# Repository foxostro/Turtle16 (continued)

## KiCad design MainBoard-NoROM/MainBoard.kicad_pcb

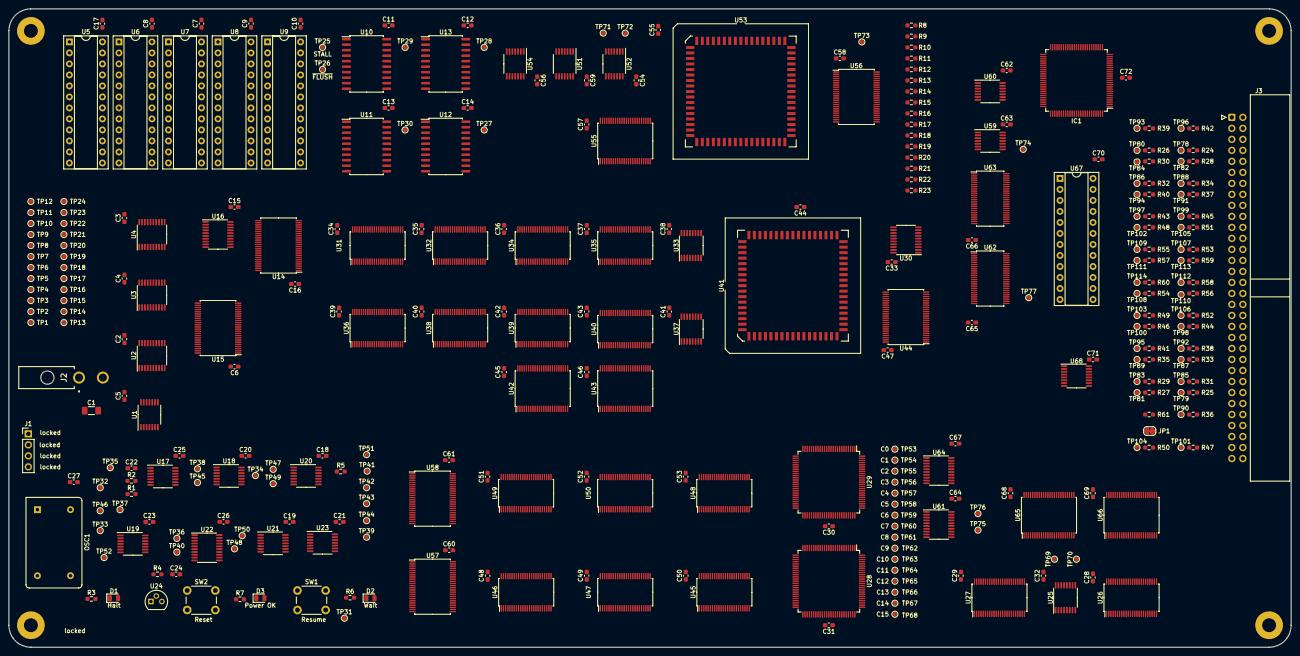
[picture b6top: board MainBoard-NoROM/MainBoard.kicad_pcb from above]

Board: 4 copper layers, 295.9 x 147.3 mm, 330 parts (0 on the bottom side), 505 nets, no tracks yet.

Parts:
C1: 100µF; C_1206_3216Metric_Pad1.33x1.80mm_HandSolder
C2, C3, C4, C5, C6, C7, C8, C9, C10, C11, C12, C13, C14, C15, C16, C17, C18, C19, C20, C21, C23, C24, C25, C26, C27, C28, C29, C30, C31, C32, C33, C34, C35, C36, C37, C38, C39, C40, C41, C42, C43, C44, C45, C46, C47, C48, C49, C50, C51, C52, C53, C54, C55, C56, C57, C58, C59, C60, C61, C62, C63, C64, C65, C66, C67, C68, C69, C70, C71, C72: 100nF; C_0603_1608Metric_Pad1.08x0.95mm_HandSolder
C22: 1uF; C_0603_1608Metric_Pad1.08x0.95mm_HandSolder
D1: Halt; LED_0805_2012Metric
D2: Wait; LED_0805_2012Metric
D3: Power OK; LED_0805_2012Metric
H1, H2, H3, H4: MountingHole_Pad; MountingHole_3.2mm_M3_Pad
IC1: 7028L20PFGI; TQFP-100_14x14mm_P0.5mm
J1: Ext Clock; PinHeader_1x04_P2.54mm_Vertical
J2: Power; 172448-0002
J3: 71922-164LF; IDC-Header_2x32_P2.54mm_Horizontal
JP1: SolderJumper_2_Bridged; SolderJumper-2_P1.3mm_Bridged_RoundedPad1.0x1.5mm
OSC1: 12MHz; Oscillator_DIP-14
R1, R5, R8, R9, R10, R11, R12, R13, R14, R15, R16, R17, R18, R19, R20, R21, R22, R23, R24, R25, R26, R27, R28, R29, R30, R31, R32, R33, R34, R35, R36, R37, R38, R39, R40, R41, R42, R43, R44, R45, R46, R47, R48, R49, R50, R51, R52, R53, R54, R55, R56, R57, R58, R59, R60, R61: 10K; R_0603_1608Metric_Pad0.98x0.95mm_HandSolder
R2, R4: 1K; R_0603_1608Metric_Pad0.98x0.95mm_HandSolder
R3, R6, R7: 270R; R_0603_1608Metric_Pad0.98x0.95mm_HandSolder
SW1: Resume; SW_PUSH_6mm_H5mm
SW2: Reset; SW_PUSH_6mm_H5mm
TP1: Ctl_Mid0; TestPoint_Pad_D1.0mm
TP2: Ctl_Mid1; TestPoint_Pad_D1.0mm
TP3: Ctl_Mid2; TestPoint_Pad_D1.0mm
TP4: Ctl_Mid3; TestPoint_Pad_D1.0mm
TP5: Ctl_Mid4; TestPoint_Pad_D1.0mm
TP6: Ctl_Mid5; TestPoint_Pad_D1.0mm
TP7: Ctl_Mid6; TestPoint_Pad_D1.0mm
TP8: Ctl_Mid7; TestPoint_Pad_D1.0mm
TP9: Ctl_Mid8; TestPoint_Pad_D1.0mm
TP10: Ctl_Mid9; TestPoint_Pad_D1.0mm
TP11: Ctl_Mid10; TestPoint_Pad_D1.0mm
TP12: Ctl_Mid11; TestPoint_Pad_D1.0mm
TP13: Ctl_Mid12; TestPoint_Pad_D1.0mm
TP14: Ctl_Mid13; TestPoint_Pad_D1.0mm
TP15: Ctl_Mid14; TestPoint_Pad_D1.0mm
TP16: Ctl_Mid15; TestPoint_Pad_D1.0mm
TP17: Ctl_Mid16; TestPoint_Pad_D1.0mm
TP18: Ctl_Mid17; TestPoint_Pad_D1.0mm
TP19: Ctl_Mid18; TestPoint_Pad_D1.0mm
TP20: Ctl_Mid19; TestPoint_Pad_D1.0mm
TP21: Ctl_Mid20; TestPoint_Pad_D1.0mm
TP22: Ctl_Mid21; TestPoint_Pad_D1.0mm
TP23: Ctl_Mid22; TestPoint_Pad_D1.0mm
TP24: Ctl_Mid23; TestPoint_Pad_D1.0mm
TP25: STALL; TestPoint_Pad_D1.0mm
TP26: ~{FLUSH}; TestPoint_Pad_D1.0mm
TP27: SEL_B_MATCHES_SEL_C_MEM; TestPoint_Pad_D1.0mm
TP28: SEL_A_MATCHES_SEL_C_MEM; TestPoint_Pad_D1.0mm
TP29: SEL_A_MATCHES_SEL_C_EX; TestPoint_Pad_D1.0mm
TP30: SEL_B_MATCHES_SEL_C_EX; TestPoint_Pad_D1.0mm
TP31: Resume; TestPoint_Pad_D1.0mm
TP32: RawClock; TestPoint_Pad_D1.0mm
TP33: ~{HLT}; TestPoint_Pad_D1.0mm
TP34, TP38: HLT; TestPoint_Pad_D1.0mm
TP35, TP40, TP41, TP47, TP49, TP50, TP69, TP70, TP71: TP; TestPoint_Pad_D1.0mm
TP36: Phi1_0; TestPoint_Pad_D1.0mm
TP37: Debounced; TestPoint_Pad_D1.0mm
TP39: Button1; TestPoint_Pad_D1.0mm
TP42: Phi1a; TestPoint_Pad_D1.0mm
TP43: Phi1b; TestPoint_Pad_D1.0mm
TP44: Phi1c; TestPoint_Pad_D1.0mm
TP45: Phi1d; TestPoint_Pad_D1.0mm
TP46: Phi2; TestPoint_Pad_D1.0mm
TP48: ~{RST_sync}; TestPoint_Pad_D1.0mm
TP51: RDY; TestPoint_Pad_D1.0mm
TP52: ~{RST_async}; TestPoint_Pad_D1.0mm
TP53: C0; TestPoint_Pad_D1.0mm
TP54: C1; TestPoint_Pad_D1.0mm
TP55: C2; TestPoint_Pad_D1.0mm
TP56: C3; TestPoint_Pad_D1.0mm
TP57: C4; TestPoint_Pad_D1.0mm
TP58: C5; TestPoint_Pad_D1.0mm
TP59: C6; TestPoint_Pad_D1.0mm
TP60: C7; TestPoint_Pad_D1.0mm
TP61: C8; TestPoint_Pad_D1.0mm
TP62: C9; TestPoint_Pad_D1.0mm
TP63: C10; TestPoint_Pad_D1.0mm
TP64: C11; TestPoint_Pad_D1.0mm
TP65: C12; TestPoint_Pad_D1.0mm
TP66: C13; TestPoint_Pad_D1.0mm
TP67: C14; TestPoint_Pad_D1.0mm
TP68: C15; TestPoint_Pad_D1.0mm
TP72: RS1; TestPoint_Pad_D1.0mm
TP73: CLK; TestPoint_Pad_D1.0mm
TP74: ~{RDY}; TestPoint_Pad_D1.0mm
TP75: ~{MemStoreIn}; TestPoint_Pad_D1.0mm
TP76: ~{MemLoadIn}; TestPoint_Pad_D1.0mm
TP77: ~{Assert}; TestPoint_Pad_D1.0mm
TP78: Addr0; TestPoint_Pad_D1.0mm
TP79: IO0; TestPoint_Pad_D1.0mm
TP80: Addr1; TestPoint_Pad_D1.0mm
TP81: IO1; TestPoint_Pad_D1.0mm
TP82: Addr2; TestPoint_Pad_D1.0mm
TP83: IO2; TestPoint_Pad_D1.0mm
TP84: Addr3; TestPoint_Pad_D1.0mm
TP85: IO3; TestPoint_Pad_D1.0mm
TP86: Addr4; TestPoint_Pad_D1.0mm
TP87: IO4; TestPoint_Pad_D1.0mm
TP88: Addr5; TestPoint_Pad_D1.0mm
TP89: IO5; TestPoint_Pad_D1.0mm
TP90: Bank0; TestPoint_Pad_D1.0mm
TP91: Addr6; TestPoint_Pad_D1.0mm
TP92: IO6; TestPoint_Pad_D1.0mm
TP93: Bank1; TestPoint_Pad_D1.0mm
TP94: Addr7; TestPoint_Pad_D1.0mm
TP95: IO7; TestPoint_Pad_D1.0mm
TP96: Bank2; TestPoint_Pad_D1.0mm
TP97: Addr8; TestPoint_Pad_D1.0mm
TP98: IO8; TestPoint_Pad_D1.0mm
TP99: Addr9; TestPoint_Pad_D1.0mm
TP100: IO9; TestPoint_Pad_D1.0mm
TP101: ~{MemStore}; TestPoint_Pad_D1.0mm
TP102: Addr10; TestPoint_Pad_D1.0mm
TP103: IO10; TestPoint_Pad_D1.0mm
TP104: ~{MemLoad}; TestPoint_Pad_D1.0mm
TP105: Addr11; TestPoint_Pad_D1.0mm
TP106: IO11; TestPoint_Pad_D1.0mm
TP107: Addr12; TestPoint_Pad_D1.0mm
TP108: IO12; TestPoint_Pad_D1.0mm
TP109: Addr13; TestPoint_Pad_D1.0mm
TP110: IO13; TestPoint_Pad_D1.0mm
TP111: Addr14; TestPoint_Pad_D1.0mm
TP112: IO14; TestPoint_Pad_D1.0mm
TP113: Addr15; TestPoint_Pad_D1.0mm
TP114: IO15; TestPoint_Pad_D1.0mm
U1, U19, U21, U52, U60: 74AHCT04; TSSOP-14_4.4x5mm_P0.65mm
U2, U3, U4, U22: 74AHCT273; TSSOP-20_4.4x6.5mm_P0.65mm
U5, U6, U7, U8, U9: ATF22V10C-7PX; DIP-24_W7.62mm_Socket
U10, U11, U12, U13: 74F521; SOIC-20W_7.5x12.8mm_P1.27mm
U14, U15, U42, U43, U44, U55, U56, U57, U58, U65, U66: 74ABT16374; TSSOP-48_8x12.5mm_P0.5mm
U16: 74AHCT574; TSSOP-20_4.4x6.5mm_P0.65mm
U17: 74HC14; TSSOP-14_4.4x5mm_P0.65mm
U18, U23: 74AHCT08; TSSOP-14_4.4x5mm_P0.65mm
U20: 74AHCT05; TSSOP-14_4.4x5mm_P0.65mm
U24: MCP100-450D; TO-92
U25, U33, U37: 74AHCT138; TSSOP-16_4.4x5mm_P0.65mm
U26, U27: 74ABT16245; TSSOP-48_6.1x12.5mm_P0.5mm
U28, U29: IDT7024L15PFG; TQFP-100_14x14mm_P0.5mm
U30: 74ABT377; TSSOP-20_4.4x6.5mm_P0.65mm
U31, U32, U34, U35, U36, U38, U39, U40, U45, U46, U47, U48, U49, U50, U62, U63: 74AHCT16245; TSSOP-48_6.1x12.5mm_P0.5mm
U41, U53: IDT7381; PLCC-68_SMD-Socket
U51, U54, U59: 74ABT32; TSSOP-14_4.4x5mm_P0.65mm
U61: 74AHCT245; TSSOP-20_4.4x6.5mm_P0.65mm
U64: 74ABT574; TSSOP-20_4.4x6.5mm_P0.65mm
U67: ATF22V10C; DIP-24_W7.62mm_Socket
U68: CD74HC173PWR; TSSOP-16_4.4x5mm_P0.65mm

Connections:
/Clock/Button1: TP39.1, U18.9, U22.2 (Q0), U22.4 (D1)
/Clock/Phi1_0: TP36.1, U17.4, U21.1, U22.11 (Cp)
/Clock/RawClock: J1.2, OSC1.8 (OUT), TP32.1, U17.3
/Clock/~RST_async: TP52.1, U19.13, U22.1 (~Mr), U22.18 (D7), U24.1 (~RST)
/Clock/~SINGLE: J1.4, U18.12
/EX/A0: U41.1 (A0), U57.2 (1Q1)
/EX/A1: U41.2 (A1), U57.3 (1Q2)
/EX/A2: U41.3 (A2), U57.5 (1Q3)
/EX/A3: U41.4 (A3), U57.6 (1Q4)
/EX/A4: U41.5 (A4), U57.8 (1Q5)
/EX/A5: U41.6 (A5), U57.9 (1Q6)
/EX/A6: U41.7 (A6), U57.11 (1Q7)
/EX/A7: U41.8 (A7), U57.12 (1Q8)
/EX/A8: U41.9 (A8), U57.13 (2Q1)
/EX/A9: U41.10 (A9), U57.14 (2Q2)
/EX/A10: U41.11 (A10), U57.16 (2Q3)
/EX/A11: U41.12 (A11), U57.17 (2Q4)
/EX/A12: U41.13 (A12), U57.19 (2Q5)
/EX/A13: U41.14 (A13), U57.20 (2Q6)
/EX/A14: U41.15 (A14), U57.22 (2Q7)
/EX/A15: U41.16 (A15), U57.23 (2Q8)
/EX/ALU/C16: U30.3 (D0), U41.20 (C16)
/EX/ALU/OVF: U30.7 (D2), U41.24 (OVF)
/EX/ALU/RightOp0: U31.2 (1B1), U32.2 (1B1), U34.2 (1B1), U35.2 (1B1), U41.53 (B0)
/EX/ALU/RightOp1: U31.3 (1B2), U32.3 (1B2), U34.3 (1B2), U35.3 (1B2), U41.54 (B1)
/EX/ALU/RightOp2: U31.5 (1B3), U32.5 (1B3), U34.5 (1B3), U35.5 (1B3), U41.55 (B2)
/EX/ALU/RightOp3: U31.6 (1B4), U32.6 (1B4), U34.6 (1B4), U35.6 (1B4), U41.56 (B3)
/EX/ALU/RightOp4: U31.8 (1B5), U32.8 (1B5), U34.8 (1B5), U35.8 (1B5), U41.57 (B4)
/EX/ALU/RightOp5: U31.9 (1B6), U32.9 (1B6), U34.9 (1B6), U35.9 (1B6), U41.58 (B5)
/EX/ALU/RightOp6: U31.11 (1B7), U32.11 (1B7), U34.11 (1B7), U35.11 (1B7), U41.59 (B6)
/EX/ALU/RightOp7: U31.12 (1B8), U32.12 (1B8), U34.12 (1B8), U35.12 (1B8), U41.60 (B7)
/EX/ALU/RightOp8: U31.13 (2B1), U32.13 (2B1), U34.13 (2B1), U35.13 (2B1), U41.61 (B8)
/EX/ALU/RightOp9: U31.14 (2B2), U32.14 (2B2), U34.14 (2B2), U35.14 (2B2), U41.62 (B9)
/EX/ALU/RightOp10: U31.16 (2B3), U32.16 (2B3), U34.16 (2B3), U35.16 (2B3), U41.63 (B10)
/EX/ALU/RightOp11: U31.17 (2B4), U32.17 (2B4), U34.17 (2B4), U35.17 (2B4), U41.64 (B11)
/EX/ALU/RightOp12: U31.19 (2B5), U32.19 (2B5), U34.19 (2B5), U35.19 (2B5), U41.65 (B12)
/EX/ALU/RightOp13: U31.20 (2B6), U32.20 (2B6), U34.20 (2B6), U35.20 (2B6), U41.66 (B13)
/EX/ALU/RightOp14: U31.22 (2B7), U32.22 (2B7), U34.22 (2B7), U35.22 (2B7), U41.67 (B14)
/EX/ALU/RightOp15: U31.23 (2B8), U32.23 (2B8), U34.23 (2B8), U35.23 (2B8), U41.68 (B15)
/EX/ALU/Z: U30.4 (D1), U41.23 (Z)
/EX/B0: U31.47 (1A1), U36.47 (1A1), U58.2 (1Q1)
/EX/B1: U31.46 (1A2), U36.46 (1A2), U58.3 (1Q2)
/EX/B2: U31.44 (1A3), U36.44 (1A3), U58.5 (1Q3)
/EX/B3: U31.43 (1A4), U36.43 (1A4), U58.6 (1Q4)
/EX/B4: U31.41 (1A5), U36.41 (1A5), U58.8 (1Q5)
/EX/B5: U31.40 (1A6), U36.40 (1A6), U58.9 (1Q6)
/EX/B6: U31.38 (1A7), U36.38 (1A7), U58.11 (1Q7)
/EX/B7: U31.37 (1A8), U36.37 (1A8), U58.12 (1Q8)
/EX/B8: U31.36 (2A1), U36.36 (2A1), U58.13 (2Q1)
/EX/B9: U31.35 (2A2), U36.35 (2A2), U58.14 (2Q2)
/EX/B10: U31.33 (2A3), U36.33 (2A3), U58.16 (2Q3)
/EX/B11: U31.32 (2A4), U36.32 (2A4), U58.17 (2Q4)
/EX/B12: U31.30 (2A5), U36.30 (2A5), U58.19 (2Q5)
/EX/B13: U31.29 (2A6), U36.29 (2A6), U58.20 (2Q6)
/EX/B14: U31.27 (2A7), U36.27 (2A7), U58.22 (2Q7)
/EX/B15: U31.26 (2A8), U36.26 (2A8), U58.23 (2Q8)
/EX/Carry: U5.4 (IN), U6.4 (IN), U7.4 (IN), U30.2 (Q0)
/EX/Ctl_MEM14: TP76.1, U42.2 (1Q1), U61.3 (A1)
/EX/Ctl_MEM15: TP75.1, U42.3 (1Q2), U61.2 (A0)
/EX/Ctl_MEM16: U42.5 (1Q3), U59.5
/EX/Ctl_MEM17: U8.4 (IN), U42.6 (1Q4), U64.9 (D7)
/EX/Ctl_MEM18: U42.8 (1Q5), U64.8 (D6)
/EX/Ctl_MEM19: U42.9 (1Q6), U64.7 (D5)
/EX/Ctl_MEM20: U8.5 (IN), U42.11 (1Q7), U64.6 (D4)
/EX/N: U5.1 (IN/CLK), U6.1 (IN/CLK), U7.1 (IN/CLK), U30.9 (Q3)
/EX/OVF: U5.2 (IN), U6.2 (IN), U7.2 (IN), U30.6 (Q2)
/EX/PC_EX0: U38.47 (1A1), U55.2 (1Q1)
/EX/PC_EX1: U38.46 (1A2), U55.3 (1Q2)
/EX/PC_EX2: U38.44 (1A3), U55.5 (1Q3)
/EX/PC_EX3: U38.43 (1A4), U55.6 (1Q4)
/EX/PC_EX4: U38.41 (1A5), U55.8 (1Q5)
/EX/PC_EX5: U38.40 (1A6), U55.9 (1Q6)
/EX/PC_EX6: U38.38 (1A7), U55.11 (1Q7)
/EX/PC_EX7: U38.37 (1A8), U55.12 (1Q8)
/EX/PC_EX8: U38.36 (2A1), U55.13 (2Q1)
/EX/PC_EX9: U38.35 (2A2), U55.14 (2Q2)
/EX/PC_EX10: U38.33 (2A3), U55.16 (2Q3)
/EX/PC_EX11: U38.32 (2A4), U55.17 (2Q4)
/EX/PC_EX12: U38.30 (2A5), U55.19 (2Q5)
/EX/PC_EX13: U38.29 (2A6), U55.20 (2Q6)
/EX/PC_EX14: U38.27 (2A7), U55.22 (2Q7)
/EX/PC_EX15: U38.26 (2A8), U55.23 (2Q8)
/EX/SelC_MEM0: U12.3 (Q0), U13.3 (Q0), U42.13 (2Q1), U64.5 (D3)
/EX/SelC_MEM1: U12.5 (Q1), U13.5 (Q1), U42.14 (2Q2), U64.4 (D2)
/EX/SelC_MEM2: U12.7 (Q2), U13.7 (Q2), U42.16 (2Q3), U64.3 (D1)
/EX/StoreOp_MEM0: U43.2 (1Q1), U62.23 (2B8)
/EX/StoreOp_MEM1: U43.3 (1Q2), U62.22 (2B7)
/EX/StoreOp_MEM2: U43.5 (1Q3), U62.20 (2B6)
/EX/StoreOp_MEM3: U43.6 (1Q4), U62.19 (2B5)
/EX/StoreOp_MEM4: U43.8 (1Q5), U62.17 (2B4)
/EX/StoreOp_MEM5: U43.9 (1Q6), U62.16 (2B3)
/EX/StoreOp_MEM6: U43.11 (1Q7), U62.14 (2B2)
/EX/StoreOp_MEM7: U43.12 (1Q8), U62.13 (2B1)
/EX/StoreOp_MEM8: U43.13 (2Q1), U62.12 (1B8)
/EX/StoreOp_MEM9: U43.14 (2Q2), U62.11 (1B7)
/EX/StoreOp_MEM10: U43.16 (2Q3), U62.9 (1B6)
/EX/StoreOp_MEM11: U43.17 (2Q4), U62.8 (1B5)
/EX/StoreOp_MEM12: U43.19 (2Q5), U62.6 (1B4)
/EX/StoreOp_MEM13: U43.20 (2Q6), U62.5 (1B3)
/EX/StoreOp_MEM14: U43.22 (2Q7), U62.3 (1B2)
/EX/StoreOp_MEM15: U43.23 (2Q8), U62.2 (1B1)
/EX/Y_EX0: U41.43 (F0), U44.47 (1D1), U46.47 (1A1), U49.47 (1A1), U53.53 (B0)
/EX/Y_EX1: U41.42 (F1), U44.46 (1D2), U46.46 (1A2), U49.46 (1A2), U53.54 (B1)
/EX/Y_EX2: U41.41 (F2), U44.44 (1D3), U46.44 (1A3), U49.44 (1A3), U53.55 (B2)
/EX/Y_EX3: U41.40 (F3), U44.43 (1D4), U46.43 (1A4), U49.43 (1A4), U53.56 (B3)
/EX/Y_EX4: U41.39 (F4), U44.41 (1D5), U46.41 (1A5), U49.41 (1A5), U53.57 (B4)
/EX/Y_EX5: U41.38 (F5), U44.40 (1D6), U46.40 (1A6), U49.40 (1A6), U53.58 (B5)
/EX/Y_EX6: U41.37 (F6), U44.38 (1D7), U46.38 (1A7), U49.38 (1A7), U53.59 (B6)
/EX/Y_EX7: U41.36 (F7), U44.37 (1D8), U46.37 (1A8), U49.37 (1A8), U53.60 (B7)
/EX/Y_EX8: U41.35 (F8), U44.36 (2D1), U46.36 (2A1), U49.36 (2A1), U53.61 (B8)
/EX/Y_EX9: U41.34 (F9), U44.35 (2D2), U46.35 (2A2), U49.35 (2A2), U53.62 (B9)
/EX/Y_EX10: U41.33 (F10), U44.33 (2D3), U46.33 (2A3), U49.33 (2A3), U53.63 (B10)
/EX/Y_EX11: U41.32 (F11), U44.32 (2D4), U46.32 (2A4), U49.32 (2A4), U53.64 (B11)
/EX/Y_EX12: U41.31 (F12), U44.30 (2D5), U46.30 (2A5), U49.30 (2A5), U53.65 (B12)
/EX/Y_EX13: U41.30 (F13), U44.29 (2D6), U46.29 (2A6), U49.29 (2A6), U53.66 (B13)
/EX/Y_EX14: U41.29 (F14), U44.27 (2D7), U46.27 (2A7), U49.27 (2A7), U53.67 (B14)
/EX/Y_EX15: U30.8 (D3), U41.28 (F15), U44.26 (2D8), U46.26 (2A8), U49.26 (2A8), U53.68 (B15)
/EX/Y_MEM0: U44.2 (1Q1), U47.47 (1A1), U50.47 (1A1), U63.2 (1B1), U66.47 (1D1)
/EX/Y_MEM1: U44.3 (1Q2), U47.46 (1A2), U50.46 (1A2), U63.3 (1B2), U66.46 (1D2)
/EX/Y_MEM2: U44.5 (1Q3), U47.44 (1A3), U50.44 (1A3), U63.5 (1B3), U66.44 (1D3)
/EX/Y_MEM3: U44.6 (1Q4), U47.43 (1A4), U50.43 (1A4), U63.6 (1B4), U66.43 (1D4)
/EX/Y_MEM4: U44.8 (1Q5), U47.41 (1A5), U50.41 (1A5), U63.8 (1B5), U66.41 (1D5)
/EX/Y_MEM5: U44.9 (1Q6), U47.40 (1A6), U50.40 (1A6), U63.9 (1B6), U66.40 (1D6)
/EX/Y_MEM6: U44.11 (1Q7), U47.38 (1A7), U50.38 (1A7), U63.11 (1B7), U66.38 (1D7)
/EX/Y_MEM7: U44.12 (1Q8), U47.37 (1A8), U50.37 (1A8), U63.12 (1B8), U66.37 (1D8)
/EX/Y_MEM8: U44.13 (2Q1), U47.36 (2A1), U50.36 (2A1), U63.13 (2B1), U66.36 (2D1)
/EX/Y_MEM9: U44.14 (2Q2), U47.35 (2A2), U50.35 (2A2), U63.14 (2B2), U66.35 (2D2)
/EX/Y_MEM10: U44.16 (2Q3), U47.33 (2A3), U50.33 (2A3), U63.16 (2B3), U66.33 (2D3)
/EX/Y_MEM11: U44.17 (2Q4), U47.32 (2A4), U50.32 (2A4), U63.17 (2B4), U66.32 (2D4)
/EX/Y_MEM12: U44.19 (2Q5), U47.30 (2A5), U50.30 (2A5), U63.19 (2B5), U66.30 (2D5)
/EX/Y_MEM13: U44.20 (2Q6), U47.29 (2A6), U50.29 (2A6), U63.20 (2B6), U66.29 (2D6)
/EX/Y_MEM14: U44.22 (2Q7), U47.27 (2A7), U50.27 (2A7), U63.22 (2B7), U66.27 (2D7)
/EX/Y_MEM15: U44.23 (2Q8), U47.26 (2A8), U50.26 (2A8), U63.23 (2B8), U66.26 (2D8)
/EX/Z: U5.3 (IN), U6.3 (IN), U7.3 (IN), U30.5 (Q1)
/EX/sheet5FD8D6EA/StoreOp_EX0: U36.2 (1B1), U38.2 (1B1), U39.2 (1B1), U40.2 (1B1), U43.47 (1D1)
/EX/sheet5FD8D6EA/StoreOp_EX1: U36.3 (1B2), U38.3 (1B2), U39.3 (1B2), U40.3 (1B2), U43.46 (1D2)
/EX/sheet5FD8D6EA/StoreOp_EX2: U36.5 (1B3), U38.5 (1B3), U39.5 (1B3), U40.5 (1B3), U43.44 (1D3)
/EX/sheet5FD8D6EA/StoreOp_EX3: U36.6 (1B4), U38.6 (1B4), U39.6 (1B4), U40.6 (1B4), U43.43 (1D4)
/EX/sheet5FD8D6EA/StoreOp_EX4: U36.8 (1B5), U38.8 (1B5), U39.8 (1B5), U40.8 (1B5), U43.41 (1D5)
/EX/sheet5FD8D6EA/StoreOp_EX5: U36.9 (1B6), U38.9 (1B6), U39.9 (1B6), U40.9 (1B6), U43.40 (1D6)
/EX/sheet5FD8D6EA/StoreOp_EX6: U36.11 (1B7), U38.11 (1B7), U39.11 (1B7), U40.11 (1B7), U43.38 (1D7)
/EX/sheet5FD8D6EA/StoreOp_EX7: U36.12 (1B8), U38.12 (1B8), U39.12 (1B8), U40.12 (1B8), U43.37 (1D8)
/EX/sheet5FD8D6EA/StoreOp_EX8: U36.13 (2B1), U38.13 (2B1), U39.13 (2B1), U40.13 (2B1), U43.36 (2D1)
/EX/sheet5FD8D6EA/StoreOp_EX9: U36.14 (2B2), U38.14 (2B2), U39.14 (2B2), U40.14 (2B2), U43.35 (2D2)
/EX/sheet5FD8D6EA/StoreOp_EX10: U36.16 (2B3), U38.16 (2B3), U39.16 (2B3), U40.16 (2B3), U43.33 (2D3)
/EX/sheet5FD8D6EA/StoreOp_EX11: U36.17 (2B4), U38.17 (2B4), U39.17 (2B4), U40.17 (2B4), U43.32 (2D4)
/EX/sheet5FD8D6EA/StoreOp_EX12: U36.19 (2B5), U38.19 (2B5), U39.19 (2B5), U40.19 (2B5), U43.30 (2D5)
/EX/sheet5FD8D6EA/StoreOp_EX13: U36.20 (2B6), U38.20 (2B6), U39.20 (2B6), U40.20 (2B6), U43.29 (2D6)
/EX/sheet5FD8D6EA/StoreOp_EX14: U36.22 (2B7), U38.22 (2B7), U39.22 (2B7), U40.22 (2B7), U43.27 (2D7)
/EX/sheet5FD8D6EA/StoreOp_EX15: U36.23 (2B8), U38.23 (2B8), U39.23 (2B8), U40.23 (2B8), U43.26 (2D8)
/ID/Ctl_EX0: TP33.1, U15.2 (1Q1), U18.13, U19.5
/ID/Ctl_EX1: U15.3 (1Q2), U37.1 (A0)
/ID/Ctl_EX2: U15.5 (1Q3), U37.2 (A1)
/ID/Ctl_EX3: U15.6 (1Q4), U33.1 (A0)
/ID/Ctl_EX4: U15.8 (1Q5), U33.2 (A1)
/ID/Ctl_EX5: U15.9 (1Q6), U30.1 (~E)
/ID/Ctl_EX6: U15.11 (1Q7), U41.44 (C0)
/ID/Ctl_EX7: U15.12 (1Q8), U41.45 (I0)
/ID/Ctl_EX8: U15.13 (2Q1), U41.46 (I1)
/ID/Ctl_EX9: U15.14 (2Q2), U41.47 (I2)
/ID/Ctl_EX10: U15.16 (2Q3), U41.48 (RS0)
/ID/Ctl_EX11: U15.17 (2Q4), U41.49 (RS1)
/ID/Ctl_EX12: U15.19 (2Q5), U52.1, U53.44 (C0)
/ID/Ctl_EX13: U15.20 (2Q6), U53.48 (RS0)
/ID/Ctl_EX14: U15.22 (2Q7), U42.47 (1D1)
/ID/Ctl_EX15: U15.23 (2Q8), U42.46 (1D2)
/ID/Ctl_EX16: U16.12 (Q7), U42.44 (1D3)
/ID/Ctl_EX17: U16.13 (Q6), U42.43 (1D4)
/ID/Ctl_EX18: U16.14 (Q5), U42.41 (1D5)
/ID/Ctl_EX19: U16.15 (Q4), U42.40 (1D6)
/ID/Ctl_EX20: U16.16 (Q3), U42.38 (1D7)
/ID/Ctl_Mid0: TP1.1, U2.3 (D0), U5.23 (I/O)
/ID/Ctl_Mid1: TP2.1, U2.4 (D1), U5.22 (I/O)
/ID/Ctl_Mid2: TP3.1, U2.7 (D2), U5.21 (I/O)
/ID/Ctl_Mid3: TP4.1, U2.8 (D3), U5.20 (I/O)
/ID/Ctl_Mid4: TP5.1, U2.13 (D4), U5.19 (I/O)
/ID/Ctl_Mid5: TP6.1, U2.14 (D5), U5.18 (I/O), U9.4 (IN)
/ID/Ctl_Mid6: TP7.1, U2.17 (D6), U5.17 (I/O)
/ID/Ctl_Mid7: TP8.1, U2.18 (D7), U5.14 (I/O)
/ID/Ctl_Mid8: TP9.1, U3.3 (D0), U5.15 (I/O)
/ID/Ctl_Mid9: TP10.1, U3.4 (D1), U5.16 (I/O)
/ID/Ctl_Mid10: TP11.1, U3.7 (D2), U6.21 (I/O)
/ID/Ctl_Mid11: TP12.1, U3.8 (D3), U6.22 (I/O)
/ID/Ctl_Mid12: TP13.1, U3.13 (D4), U6.23 (I/O), U9.5 (IN)
/ID/Ctl_Mid13: TP14.1, U3.14 (D5), U6.20 (I/O)
/ID/Ctl_Mid14: TP15.1, U3.17 (D6), U6.19 (I/O)
/ID/Ctl_Mid15: TP16.1, U3.18 (D7), U6.18 (I/O)
/ID/Ctl_Mid16: TP17.1, U4.3 (D0), U6.17 (I/O)
/ID/Ctl_Mid17: TP18.1, U4.4 (D1), U6.16 (I/O), U8.2 (IN)
/ID/Ctl_Mid18: TP19.1, U4.7 (D2), U6.15 (I/O)
/ID/Ctl_Mid19: TP20.1, U4.8 (D3), U6.14 (I/O)
/ID/Ctl_Mid20: TP21.1, U4.13 (D4), U7.23 (I/O), U8.3 (IN)
/ID/Ctl_Mid21: TP22.1, U4.14 (D5), U7.22 (I/O), U8.10 (IN)
/ID/Ctl_Mid22: TP23.1, U4.17 (D6), U7.21 (I/O), U8.11 (IN)
/ID/Ctl_Mid23: TP24.1, U4.18 (D7), U7.20 (I/O)
/ID/FWD_A: U8.21 (I/O), U45.25 (2~OE), U45.48 (1~OE)
/ID/FWD_B: U8.20 (I/O), U48.25 (2~OE), U48.48 (1~OE)
/ID/FWD_EX_TO_A: U8.22 (I/O), U46.25 (2~OE), U46.48 (1~OE)
/ID/FWD_EX_TO_B: U8.19 (I/O), U49.25 (2~OE), U49.48 (1~OE)
/ID/FWD_MEM_TO_A: U8.23 (I/O), U47.25 (2~OE), U47.48 (1~OE)
/ID/FWD_MEM_TO_B: U8.18 (I/O), U50.25 (2~OE), U50.48 (1~OE)
/ID/Hazard Control/Hazard Control Comparators/SEL_A_MATCHES_SEL_C_EX: TP29.1, U8.6 (IN), U10.19 (~P=Q)
/ID/Hazard Control/Hazard Control Comparators/SEL_A_MATCHES_SEL_C_MEM: TP28.1, U8.8 (IN), U13.19 (~P=Q)
/ID/Hazard Control/Hazard Control Comparators/SEL_B_MATCHES_SEL_C_EX: TP30.1, U8.7 (IN), U11.19 (~P=Q)
/ID/Hazard Control/Hazard Control Comparators/SEL_B_MATCHES_SEL_C_MEM: TP27.1, U8.9 (IN), U12.19 (~P=Q)
/ID/Hazard Control/STALL: TP25.1, U9.23 (I/O), U53.25 (~ENF), U54.2
/ID/Hazard Control/~FLUSH: TP26.1, U2.1 (~Mr), U3.1 (~Mr), U4.1 (~Mr), U9.22 (I/O)
/ID/ID Flush/Ctl_ID0: U2.2 (Q0), U15.47 (1D1)
/ID/ID Flush/Ctl_ID1: U2.5 (Q1), U15.46 (1D2)
/ID/ID Flush/Ctl_ID2: U2.6 (Q2), U15.44 (1D3)
/ID/ID Flush/Ctl_ID3: U2.9 (Q3), U15.43 (1D4)
/ID/ID Flush/Ctl_ID4: U2.12 (Q4), U15.41 (1D5)
/ID/ID Flush/Ctl_ID5: U2.15 (Q5), U15.40 (1D6)
/ID/ID Flush/Ctl_ID6: U2.16 (Q6), U15.38 (1D7)
/ID/ID Flush/Ctl_ID7: U2.19 (Q7), U15.37 (1D8)
/ID/ID Flush/Ctl_ID8: U3.2 (Q0), U15.36 (2D1)
/ID/ID Flush/Ctl_ID9: U3.5 (Q1), U15.35 (2D2)
/ID/ID Flush/Ctl_ID10: U3.6 (Q2), U15.33 (2D3)
/ID/ID Flush/Ctl_ID11: U3.9 (Q3), U15.32 (2D4)
/ID/ID Flush/Ctl_ID12: U3.12 (Q4), U15.30 (2D5)
/ID/ID Flush/Ctl_ID13: U3.15 (Q5), U15.29 (2D6)
/ID/ID Flush/Ctl_ID14: U3.16 (Q6), U15.27 (2D7)
/ID/ID Flush/Ctl_ID15: U3.19 (Q7), U15.26 (2D8)
/ID/ID Flush/Ctl_ID16: U4.2 (Q0), U16.9 (D7)
/ID/ID Flush/Ctl_ID17: U4.5 (Q1), U16.8 (D6)
/ID/ID Flush/Ctl_ID18: U4.6 (Q2), U16.7 (D5)
/ID/ID Flush/Ctl_ID19: U4.9 (Q3), U16.6 (D4)
/ID/ID Flush/Ctl_ID20: U4.12 (Q4), U16.5 (D3)
/ID/ID Flush/Ctl_ID21: U4.15 (Q5), U16.4 (D2)
/ID/ID Flush/Ctl_ID22: U4.16 (Q6), U16.3 (D1)
/ID/ID Flush/Ctl_ID23: U4.19 (Q7), U16.2 (D0)
/ID/Ins_EX0: U14.2 (1Q1), U32.47 (1A1), U34.47 (1A1), U35.47 (1A1), U39.47 (1A1), U40.36 (2A1)
/ID/Ins_EX1: U14.3 (1Q2), U32.46 (1A2), U34.46 (1A2), U35.46 (1A2), U39.46 (1A2), U40.35 (2A2)
/ID/Ins_EX2: U14.5 (1Q3), U32.44 (1A3), U35.44 (1A3), U39.44 (1A3), U40.33 (2A3)
/ID/Ins_EX3: U14.6 (1Q4), U32.43 (1A4), U35.43 (1A4), U39.43 (1A4), U40.32 (2A4)
/ID/Ins_EX4: U14.8 (1Q5), U32.26 (2A8), U32.27 (2A7), U32.29 (2A6), U32.30 (2A5), U32.32 (2A4), U32.33 (2A3), U32.35 (2A2), U32.36 (2A1), U32.37 (1A8), U32.38 (1A7), U32.40 (1A6), U32.41 (1A5), U35.41 (1A5), U39.41 (1A5), U40.30 (2A5)
/ID/Ins_EX5: U14.9 (1Q6), U35.40 (1A6), U39.40 (1A6), U40.29 (2A6)
/ID/Ins_EX6: U14.11 (1Q7), U35.38 (1A7), U39.38 (1A7), U40.27 (2A7)
/ID/Ins_EX7: U14.12 (1Q8), U35.37 (1A8), U39.26 (2A8), U39.27 (2A7), U39.29 (2A6), U39.30 (2A5), U39.32 (2A4), U39.33 (2A3), U39.35 (2A2), U39.36 (2A1), U39.37 (1A8), U40.26 (2A8)
/ID/Ins_EX8: U10.3 (Q0), U11.3 (Q0), U14.13 (2Q1), U34.44 (1A3), U35.36 (2A1), U42.36 (2D1)
/ID/Ins_EX9: U10.5 (Q1), U11.5 (Q1), U14.14 (2Q2), U34.43 (1A4), U35.35 (2A2), U42.35 (2D2)
/ID/Ins_EX10: U10.7 (Q2), U11.7 (Q2), U14.16 (2Q3), U34.26 (2A8), U34.27 (2A7), U34.29 (2A6), U34.30 (2A5), U34.32 (2A4), U34.33 (2A3), U34.35 (2A2), U34.36 (2A1), U34.37 (1A8), U34.38 (1A7), U34.40 (1A6), U34.41 (1A5), U35.26 (2A8), U35.27 (2A7), U35.29 (2A6), U35.30 (2A5), U35.32 (2A4), U35.33 (2A3), U42.33 (2D3)
/ID/Ins_ID0: U14.47 (1D1), U56.2 (1Q1)
/ID/Ins_ID1: U14.46 (1D2), U56.3 (1Q2)
/ID/Ins_ID2: U11.2 (P0), U12.2 (P0), U14.44 (1D3), U29.59 (A0R), U56.5 (1Q3)
/ID/Ins_ID3: U11.4 (P1), U12.4 (P1), U14.43 (1D4), U29.58 (A1R), U56.6 (1Q4)
/ID/Ins_ID4: U11.6 (P2), U12.6 (P2), U14.41 (1D5), U29.57 (A2R), U56.8 (1Q5)
/ID/Ins_ID5: U10.2 (P0), U13.2 (P0), U14.40 (1D6), U28.59 (A0R), U56.9 (1Q6)
/ID/Ins_ID6: U10.4 (P1), U13.4 (P1), U14.38 (1D7), U28.58 (A1R), U56.11 (1Q7)
/ID/Ins_ID7: U10.6 (P2), U13.6 (P2), U14.37 (1D8), U28.57 (A2R), U56.12 (1Q8)
/ID/Ins_ID8: U14.36 (2D1), U56.13 (2Q1)
/ID/Ins_ID9: U14.35 (2D2), U56.14 (2Q2)
/ID/Ins_ID10: U14.33 (2D3), U56.16 (2Q3)
/ID/Ins_ID11: U5.9 (IN), U6.9 (IN), U7.9 (IN), U56.17 (2Q4)
/ID/Ins_ID12: U5.8 (IN), U6.8 (IN), U7.8 (IN), U56.19 (2Q5)
/ID/Ins_ID13: U5.7 (IN), U6.7 (IN), U7.7 (IN), U56.20 (2Q6)
/ID/Ins_ID14: U5.6 (IN), U6.6 (IN), U7.6 (IN), U9.2 (IN), U56.22 (2Q7)
/ID/Ins_ID15: U5.5 (IN), U6.5 (IN), U7.5 (IN), U9.3 (IN), U56.23 (2Q8)
/IF/FLUSH_IF: IC1.59 (~OER), U51.3
/MEM/Buffer StoreOp As Bus I/O/~Assert: TP77.1, U59.6, U62.25 (2~OE), U62.48 (1~OE)
/MEM/Ctl_WB17: U25.1 (A0), U64.12 (Q7)
/MEM/Ctl_WB18: U28.83 (~LBL), U29.83 (~LBL), U64.13 (Q6)
/MEM/Ctl_WB19: U28.84 (~UBL), U29.84 (~UBL), U64.14 (Q5)
/MEM/Ctl_WB20: U28.87 (R/~WL), U29.87 (R/~WL), U64.15 (Q4)
/MEM/SelC_WB0: U28.66 (A0L), U29.66 (A0L), U64.16 (Q3)
/MEM/SelC_WB1: U28.67 (A1L), U29.67 (A1L), U64.17 (Q2)
/MEM/SelC_WB2: U28.68 (A2L), U29.68 (A2L), U64.18 (Q1)
/MEM/StoreOp_WB0: U27.47 (1A1), U65.2 (1Q1)
/MEM/StoreOp_WB1: U27.46 (1A2), U65.3 (1Q2)
/MEM/StoreOp_WB2: U27.44 (1A3), U65.5 (1Q3)
/MEM/StoreOp_WB3: U27.43 (1A4), U65.6 (1Q4)
/MEM/StoreOp_WB4: U27.41 (1A5), U65.8 (1Q5)
/MEM/StoreOp_WB5: U27.40 (1A6), U65.9 (1Q6)
/MEM/StoreOp_WB6: U27.38 (1A7), U65.11 (1Q7)
/MEM/StoreOp_WB7: U27.37 (1A8), U65.12 (1Q8)
/MEM/StoreOp_WB8: U27.36 (2A1), U65.13 (2Q1)
/MEM/StoreOp_WB9: U27.35 (2A2), U65.14 (2Q2)
/MEM/StoreOp_WB10: U27.33 (2A3), U65.16 (2Q3)
/MEM/StoreOp_WB11: U27.32 (2A4), U65.17 (2Q4)
/MEM/StoreOp_WB12: U27.30 (2A5), U65.19 (2Q5)
/MEM/StoreOp_WB13: U27.29 (2A6), U65.20 (2Q6)
/MEM/StoreOp_WB14: U27.27 (2A7), U65.22 (2Q7)
/MEM/StoreOp_WB15: U27.26 (2A8), U65.23 (2Q8)
/MEM/Y_WB0: U26.47 (1A1), U66.2 (1Q1)
/MEM/Y_WB1: U26.46 (1A2), U66.3 (1Q2)
/MEM/Y_WB2: U26.44 (1A3), U66.5 (1Q3)
/MEM/Y_WB3: U26.43 (1A4), U66.6 (1Q4)
/MEM/Y_WB4: U26.41 (1A5), U66.8 (1Q5)
/MEM/Y_WB5: U26.40 (1A6), U66.9 (1Q6)
/MEM/Y_WB6: U26.38 (1A7), U66.11 (1Q7)
/MEM/Y_WB7: U26.37 (1A8), U66.12 (1Q8)
/MEM/Y_WB8: U26.36 (2A1), U66.13 (2Q1)
/MEM/Y_WB9: U26.35 (2A2), U66.14 (2Q2)
/MEM/Y_WB10: U26.33 (2A3), U66.16 (2Q3)
/MEM/Y_WB11: U26.32 (2A4), U66.17 (2Q4)
/MEM/Y_WB12: U26.30 (2A5), U66.19 (2Q5)
/MEM/Y_WB13: U26.29 (2A6), U66.20 (2Q6)
/MEM/Y_WB14: U26.27 (2A7), U66.22 (2Q7)
/MEM/Y_WB15: U26.26 (2A8), U66.23 (2Q8)
/MEM/~RDY: TP74.1, U59.3, U59.4, U61.19 (CE), U63.25 (2~OE), U63.48 (1~OE)
/Operand Forwarding A/A_ID0: U45.2 (1B1), U46.2 (1B1), U47.2 (1B1), U57.47 (1D1)
/Operand Forwarding A/A_ID1: U45.3 (1B2), U46.3 (1B2), U47.3 (1B2), U57.46 (1D2)
/Operand Forwarding A/A_ID2: U45.5 (1B3), U46.5 (1B3), U47.5 (1B3), U57.44 (1D3)
/Operand Forwarding A/A_ID3: U45.6 (1B4), U46.6 (1B4), U47.6 (1B4), U57.43 (1D4)
/Operand Forwarding A/A_ID4: U45.8 (1B5), U46.8 (1B5), U47.8 (1B5), U57.41 (1D5)
/Operand Forwarding A/A_ID5: U45.9 (1B6), U46.9 (1B6), U47.9 (1B6), U57.40 (1D6)
/Operand Forwarding A/A_ID6: U45.11 (1B7), U46.11 (1B7), U47.11 (1B7), U57.38 (1D7)
/Operand Forwarding A/A_ID7: U45.12 (1B8), U46.12 (1B8), U47.12 (1B8), U57.37 (1D8)
/Operand Forwarding A/A_ID8: U45.13 (2B1), U46.13 (2B1), U47.13 (2B1), U57.36 (2D1)
/Operand Forwarding A/A_ID9: U45.14 (2B2), U46.14 (2B2), U47.14 (2B2), U57.35 (2D2)
/Operand Forwarding A/A_ID10: U45.16 (2B3), U46.16 (2B3), U47.16 (2B3), U57.33 (2D3)
/Operand Forwarding A/A_ID11: U45.17 (2B4), U46.17 (2B4), U47.17 (2B4), U57.32 (2D4)
/Operand Forwarding A/A_ID12: U45.19 (2B5), U46.19 (2B5), U47.19 (2B5), U57.30 (2D5)
/Operand Forwarding A/A_ID13: U45.20 (2B6), U46.20 (2B6), U47.20 (2B6), U57.29 (2D6)
/Operand Forwarding A/A_ID14: U45.22 (2B7), U46.22 (2B7), U47.22 (2B7), U57.27 (2D7)
/Operand Forwarding A/A_ID15: U45.23 (2B8), U46.23 (2B8), U47.23 (2B8), U57.26 (2D8)
/Operand Forwarding A/RegisterA0: U28.14 (I/O0R), U45.47 (1A1)
/Operand Forwarding A/RegisterA1: U28.15 (I/O1R), U45.46 (1A2)
/Operand Forwarding A/RegisterA2: U28.16 (I/O2R), U45.44 (1A3)
/Operand Forwarding A/RegisterA3: U28.18 (I/O3R), U45.43 (1A4)
/Operand Forwarding A/RegisterA4: U28.19 (I/O4R), U45.41 (1A5)
/Operand Forwarding A/RegisterA5: U28.20 (I/O5R), U45.40 (1A6)
/Operand Forwarding A/RegisterA6: U28.21 (I/O6R), U45.38 (1A7)
/Operand Forwarding A/RegisterA7: U28.26 (I/O7R), U45.37 (1A8)
/Operand Forwarding A/RegisterA8: U28.27 (I/O8R), U45.36 (2A1)
/Operand Forwarding A/RegisterA9: U28.28 (I/O9R), U45.35 (2A2)
/Operand Forwarding A/RegisterA10: U28.29 (I/O10R), U45.33 (2A3)
/Operand Forwarding A/RegisterA11: U28.30 (I/O11R), U45.32 (2A4)
/Operand Forwarding A/RegisterA12: U28.31 (I/O12R), U45.30 (2A5)
/Operand Forwarding A/RegisterA13: U28.32 (I/O13R), U45.29 (2A6)
/Operand Forwarding A/RegisterA14: U28.33 (I/O14R), U45.27 (2A7)
/Operand Forwarding A/RegisterA15: U28.35 (I/O15R), U45.26 (2A8)
/Operand Forwarding B/B_ID0: U48.2 (1B1), U49.2 (1B1), U50.2 (1B1), U58.47 (1D1)
/Operand Forwarding B/B_ID1: U48.3 (1B2), U49.3 (1B2), U50.3 (1B2), U58.46 (1D2)
/Operand Forwarding B/B_ID2: U48.5 (1B3), U49.5 (1B3), U50.5 (1B3), U58.44 (1D3)
/Operand Forwarding B/B_ID3: U48.6 (1B4), U49.6 (1B4), U50.6 (1B4), U58.43 (1D4)
/Operand Forwarding B/B_ID4: U48.8 (1B5), U49.8 (1B5), U50.8 (1B5), U58.41 (1D5)
/Operand Forwarding B/B_ID5: U48.9 (1B6), U49.9 (1B6), U50.9 (1B6), U58.40 (1D6)
/Operand Forwarding B/B_ID6: U48.11 (1B7), U49.11 (1B7), U50.11 (1B7), U58.38 (1D7)
/Operand Forwarding B/B_ID7: U48.12 (1B8), U49.12 (1B8), U50.12 (1B8), U58.37 (1D8)
/Operand Forwarding B/B_ID8: U48.13 (2B1), U49.13 (2B1), U50.13 (2B1), U58.36 (2D1)
/Operand Forwarding B/B_ID9: U48.14 (2B2), U49.14 (2B2), U50.14 (2B2), U58.35 (2D2)
/Operand Forwarding B/B_ID10: U48.16 (2B3), U49.16 (2B3), U50.16 (2B3), U58.33 (2D3)
/Operand Forwarding B/B_ID11: U48.17 (2B4), U49.17 (2B4), U50.17 (2B4), U58.32 (2D4)
/Operand Forwarding B/B_ID12: U48.19 (2B5), U49.19 (2B5), U50.19 (2B5), U58.30 (2D5)
/Operand Forwarding B/B_ID13: U48.20 (2B6), U49.20 (2B6), U50.20 (2B6), U58.29 (2D6)
/Operand Forwarding B/B_ID14: U48.22 (2B7), U49.22 (2B7), U50.22 (2B7), U58.27 (2D7)
/Operand Forwarding B/B_ID15: U48.23 (2B8), U49.23 (2B8), U50.23 (2B8), U58.26 (2D8)
/Operand Forwarding B/RegisterB0: U29.14 (I/O0R), U48.47 (1A1)
/Operand Forwarding B/RegisterB1: U29.15 (I/O1R), U48.46 (1A2)
/Operand Forwarding B/RegisterB2: U29.16 (I/O2R), U48.44 (1A3)
/Operand Forwarding B/RegisterB3: U29.18 (I/O3R), U48.43 (1A4)
/Operand Forwarding B/RegisterB4: U29.19 (I/O4R), U48.41 (1A5)
/Operand Forwarding B/RegisterB5: U29.20 (I/O5R), U48.40 (1A6)
/Operand Forwarding B/RegisterB6: U29.21 (I/O6R), U48.38 (1A7)
/Operand Forwarding B/RegisterB7: U29.26 (I/O7R), U48.37 (1A8)
/Operand Forwarding B/RegisterB8: U29.27 (I/O8R), U48.36 (2A1)
/Operand Forwarding B/RegisterB9: U29.28 (I/O9R), U48.35 (2A2)
/Operand Forwarding B/RegisterB10: U29.29 (I/O10R), U48.33 (2A3)
/Operand Forwarding B/RegisterB11: U29.30 (I/O11R), U48.32 (2A4)
/Operand Forwarding B/RegisterB12: U29.31 (I/O12R), U48.30 (2A5)
/Operand Forwarding B/RegisterB13: U29.32 (I/O13R), U48.29 (2A6)
/Operand Forwarding B/RegisterB14: U29.33 (I/O14R), U48.27 (2A7)
/Operand Forwarding B/RegisterB15: U29.35 (I/O15R), U48.26 (2A8)
/Phi1a: TP42.1, U23.3, U30.11 (CP), U42.25 (2CLK), U42.48 (1CLK), U43.25 (2CLK), U43.48 (1CLK), U44.25 (2CLK), U44.48 (1CLK), U53.17 (CLK), U54.1
/Phi1b: TP43.1, U23.6, U64.11 (Cp), U65.25 (2CLK), U65.48 (1CLK), U66.25 (2CLK), U66.48 (1CLK), U68.7 (Cp)
/Phi1c: TP44.1, U1.1, U14.25 (2CLK), U14.48 (1CLK), U15.25 (2CLK), U15.48 (1CLK), U16.11 (Cp), U23.8
/Phi1d: TP45.1, U23.11, U57.25 (2CLK), U57.48 (1CLK), U58.25 (2CLK), U58.48 (1CLK)
/Phi2: J3.55, TP46.1, U21.10
/RAM/Addr0: IC1.92 (A0L), J3.7, R24.1, TP78.1, U63.47 (1A1), U67.1 (IN/CLK)
/RAM/Addr1: IC1.93 (A1L), J3.8, R26.1, TP80.1, U63.46 (1A2), U67.2 (IN)
/RAM/Addr2: IC1.94 (A2L), J3.9, R28.1, TP82.1, U63.44 (1A3), U67.3 (IN)
/RAM/Addr3: IC1.95 (A3L), J3.10, R30.1, TP84.1, U63.43 (1A4), U67.4 (IN)
/RAM/Addr4: IC1.96 (A4L), J3.13, R32.1, TP86.1, U63.41 (1A5), U67.5 (IN)
/RAM/Addr5: IC1.97 (A5L), J3.14, R34.1, TP88.1, U63.40 (1A6), U67.6 (IN)
/RAM/Addr6: IC1.98 (A6L), J3.15, R37.1, TP91.1, U63.38 (1A7), U67.7 (IN)
/RAM/Addr7: IC1.99 (A7L), J3.16, R40.1, TP94.1, U63.37 (1A8), U67.8 (IN)
/RAM/Addr8: IC1.100 (A8L), J3.19, R43.1, TP97.1, U63.36 (2A1), U67.9 (IN)
/RAM/Addr9: IC1.1 (A9L), J3.20, R45.1, TP99.1, U63.35 (2A2), U67.10 (IN)
/RAM/Addr10: IC1.2 (A10L), J3.21, R48.1, TP102.1, U63.33 (2A3), U67.11 (IN)
/RAM/Addr11: IC1.3 (A11L), J3.22, R51.1, TP105.1, U63.32 (2A4), U67.13 (IN/~OE)
/RAM/Addr12: IC1.4 (A12L), J3.25, R53.1, TP107.1, U63.30 (2A5), U67.14 (I/O)
/RAM/Addr13: IC1.5 (A13L), J3.26, R55.1, TP109.1, U63.29 (2A6), U67.15 (I/O)
/RAM/Addr14: IC1.6 (A14L), J3.27, R57.1, TP111.1, U63.27 (2A7), U67.16 (I/O)
/RAM/Addr15: IC1.7 (A15L), J3.28, R59.1, TP113.1, U63.26 (2A8), U67.17 (I/O)
/RAM/Bank0: J3.56, R36.1, TP90.1, U67.18 (I/O), U68.3 (Q0)
/RAM/Bank1: J3.3, R39.1, TP93.1, U67.19 (I/O), U68.4 (Q1)
/RAM/Bank2: J3.4, R42.1, TP96.1, U67.20 (I/O), U68.5 (Q2)
/RAM/IO0: IC1.37 (I/O0L), J3.51, R25.1, TP79.1, U62.26 (2A8), U65.47 (1D1), U68.14 (D0)
/RAM/IO1: IC1.36 (I/O1L), J3.52, R27.1, TP81.1, U62.27 (2A7), U65.46 (1D2), U68.13 (D1)
/RAM/IO2: IC1.34 (I/O2L), J3.49, R29.1, TP83.1, U62.29 (2A6), U65.44 (1D3), U68.12 (D2)
/RAM/IO3: IC1.33 (I/O3L), J3.50, R31.1, TP85.1, U62.30 (2A5), U65.43 (1D4), U68.11 (D3)
/RAM/IO4: IC1.32 (I/O4L), J3.45, R33.1, TP87.1, U62.32 (2A4), U65.41 (1D5)
/RAM/IO5: IC1.31 (I/O5L), J3.46, R35.1, TP89.1, U62.33 (2A3), U65.40 (1D6)
/RAM/IO6: IC1.30 (I/O6L), J3.43, R38.1, TP92.1, U62.35 (2A2), U65.38 (1D7)
/RAM/IO7: IC1.29 (I/O7L), J3.44, R41.1, TP95.1, U62.36 (2A1), U65.37 (1D8)
/RAM/IO8: IC1.27 (I/O8L), J3.39, R44.1, TP98.1, U62.37 (1A8), U65.36 (2D1)
/RAM/IO9: IC1.26 (I/O9L), J3.40, R46.1, TP100.1, U62.38 (1A7), U65.35 (2D2)
/RAM/IO10: IC1.25 (I/O10L), J3.37, R49.1, TP103.1, U62.40 (1A6), U65.33 (2D3)
/RAM/IO11: IC1.24 (I/O11L), J3.38, R52.1, TP106.1, U62.41 (1A5), U65.32 (2D4)
/RAM/IO12: IC1.23 (I/O12L), J3.33, R54.1, TP108.1, U62.43 (1A4), U65.30 (2D5)
/RAM/IO13: IC1.22 (I/O13L), J3.34, R56.1, TP110.1, U62.44 (1A3), U65.29 (2D6)
/RAM/IO14: IC1.21 (I/O14L), J3.31, R58.1, TP112.1, U62.46 (1A2), U65.27 (2D7)
/RAM/IO15: IC1.20 (I/O15L), J3.32, R60.1, TP114.1, U62.47 (1A1), U65.26 (2D8)
/RAM/Ins_IF0: IC1.39 (I/O0R), R8.1, U56.47 (1D1)
/RAM/Ins_IF1: IC1.40 (I/O1R), R9.1, U56.46 (1D2)
/RAM/Ins_IF2: IC1.41 (I/O2R), R10.1, U56.44 (1D3)
/RAM/Ins_IF3: IC1.42 (I/O3R), R11.1, U56.43 (1D4)
/RAM/Ins_IF4: IC1.43 (I/O4R), R12.1, U56.41 (1D5)
/RAM/Ins_IF5: IC1.44 (I/O5R), R13.1, U56.40 (1D6)
/RAM/Ins_IF6: IC1.45 (I/O6R), R14.1, U56.38 (1D7)
/RAM/Ins_IF7: IC1.47 (I/O7R), R15.1, U56.37 (1D8)
/RAM/Ins_IF8: IC1.48 (I/O8R), R16.1, U56.36 (2D1)
/RAM/Ins_IF9: IC1.49 (I/O9R), R17.1, U56.35 (2D2)
/RAM/Ins_IF10: IC1.51 (I/O10R), R18.1, U56.33 (2D3)
/RAM/Ins_IF11: IC1.52 (I/O11R), R19.1, U56.32 (2D4)
/RAM/Ins_IF12: IC1.53 (I/O12R), R20.1, U56.30 (2D5)
/RAM/Ins_IF13: IC1.54 (I/O13R), R21.1, U56.29 (2D6)
/RAM/Ins_IF14: IC1.55 (I/O14R), R22.1, U56.27 (2D7)
/RAM/Ins_IF15: IC1.56 (I/O15R), R23.1, U56.26 (2D8)
/RAM/PC0: IC1.84 (A0R), U53.1 (A0), U53.43 (F0), U55.47 (1D1)
/RAM/PC1: IC1.83 (A1R), U53.2 (A1), U53.42 (F1), U55.46 (1D2)
/RAM/PC2: IC1.82 (A2R), U53.3 (A2), U53.41 (F2), U55.44 (1D3)
/RAM/PC3: IC1.81 (A3R), U53.4 (A3), U53.40 (F3), U55.43 (1D4)
/RAM/PC4: IC1.80 (A4R), U53.5 (A4), U53.39 (F4), U55.41 (1D5)
/RAM/PC5: IC1.79 (A5R), U53.6 (A5), U53.38 (F5), U55.40 (1D6)
/RAM/PC6: IC1.78 (A6R), U53.7 (A6), U53.37 (F6), U55.38 (1D7)
/RAM/PC7: IC1.77 (A7R), U53.8 (A7), U53.36 (F7), U55.37 (1D8)
/RAM/PC8: IC1.76 (A8R), U53.9 (A8), U53.35 (F8), U55.36 (2D1)
/RAM/PC9: IC1.75 (A9R), U53.10 (A9), U53.34 (F9), U55.35 (2D2)
/RAM/PC10: IC1.74 (A10R), U53.11 (A10), U53.33 (F10), U55.33 (2D3)
/RAM/PC11: IC1.73 (A11R), U53.12 (A11), U53.32 (F11), U55.32 (2D4)
/RAM/PC12: IC1.72 (A12R), U53.13 (A12), U53.31 (F12), U55.30 (2D5)
/RAM/PC13: IC1.71 (A13R), U53.14 (A13), U53.30 (F13), U55.29 (2D6)
/RAM/PC14: IC1.70 (A14R), U53.15 (A14), U53.29 (F14), U55.27 (2D7)
/RAM/PC15: IC1.69 (A15R), U53.16 (A15), U53.28 (F15), U55.26 (2D8)
/RDY: J3.59, JP1.1 (A), R5.2, TP51.1, U20.2, U21.9, U23.2, U23.5, U23.10, U23.13, U60.1
/System Bus Connector/~MemLoad: IC1.17 (~OEL), J3.62, R50.1, TP104.1, U61.17 (B1)
/System Bus Connector/~MemStore: IC1.16 (R/~WL), J3.61, R47.1, TP101.1, U61.18 (B0)
/Write Back and Register File/Select Write Back Source/C0: TP53.1, U26.2 (1B1), U27.2 (1B1), U28.90 (I/O0L), U29.90 (I/O0L)
/Write Back and Register File/Select Write Back Source/C1: TP54.1, U26.3 (1B2), U27.3 (1B2), U28.91 (I/O1L), U29.91 (I/O1L)
/Write Back and Register File/Select Write Back Source/C2: TP55.1, U26.5 (1B3), U27.5 (1B3), U28.93 (I/O2L), U29.93 (I/O2L)
/Write Back and Register File/Select Write Back Source/C3: TP56.1, U26.6 (1B4), U27.6 (1B4), U28.94 (I/O3L), U29.94 (I/O3L)
/Write Back and Register File/Select Write Back Source/C4: TP57.1, U26.8 (1B5), U27.8 (1B5), U28.95 (I/O4L), U29.95 (I/O4L)
/Write Back and Register File/Select Write Back Source/C5: TP58.1, U26.9 (1B6), U27.9 (1B6), U28.96 (I/O5L), U29.96 (I/O5L)
/Write Back and Register File/Select Write Back Source/C6: TP59.1, U26.11 (1B7), U27.11 (1B7), U28.97 (I/O6L), U29.97 (I/O6L)
/Write Back and Register File/Select Write Back Source/C7: TP60.1, U26.12 (1B8), U27.12 (1B8), U28.98 (I/O7L), U29.98 (I/O7L)
/Write Back and Register File/Select Write Back Source/C8: TP61.1, U26.13 (2B1), U27.13 (2B1), U28.99 (I/O8L), U29.99 (I/O8L)
/Write Back and Register File/Select Write Back Source/C9: TP62.1, U26.14 (2B2), U27.14 (2B2), U28.100 (I/O9L), U29.100 (I/O9L)
/Write Back and Register File/Select Write Back Source/C10: TP63.1, U26.16 (2B3), U27.16 (2B3), U28.5 (I/O10L), U29.5 (I/O10L)
/Write Back and Register File/Select Write Back Source/C11: TP64.1, U26.17 (2B4), U27.17 (2B4), U28.6 (I/O11L), U29.6 (I/O11L)
/Write Back and Register File/Select Write Back Source/C12: TP65.1, U26.19 (2B5), U27.19 (2B5), U28.7 (I/O12L), U29.7 (I/O12L)
/Write Back and Register File/Select Write Back Source/C13: TP66.1, U26.20 (2B6), U27.20 (2B6), U28.8 (I/O13L), U29.8 (I/O13L)
/Write Back and Register File/Select Write Back Source/C14: TP67.1, U26.22 (2B7), U27.22 (2B7), U28.10 (I/O14L), U29.10 (I/O14L)
/Write Back and Register File/Select Write Back Source/C15: TP68.1, U26.23 (2B8), U27.23 (2B8), U28.11 (I/O15L), U29.11 (I/O15L)
/~RST_sync: J3.60, TP48.1, U9.10 (IN), U18.1, U22.19 (Q7), U52.3, U53.45 (I0), U53.46 (I1), U60.3, U60.13
GND: C1.2, C2.2, C3.2, C4.2, C5.2, C6.2, C7.2, C8.2, C9.2, C10.2, C11.2, C12.2, C13.2, C14.2, C15.2, C16.2, C17.2, C18.2, C19.2, C20.2, C21.2, C22.2, C23.2, C24.2, C25.2, C26.2, C27.2, C28.2, C29.2, C30.2, C31.2, C32.2, C33.2, C34.2, C35.2, C36.2, C37.2, C38.2, C39.2, C40.2, C41.2, C42.2, C43.2, C44.2, C45.2, C46.2, C47.2, C48.2, C49.2, C50.2, C51.2, C52.2, C53.2, C54.2, C55.2, C56.2, C57.2, C58.2, C59.2, C60.2, C61.2, C62.2, C63.2, C64.2, C65.2, C66.2, C67.2, C68.2, C69.2, C70.2, C71.2, C72.2, H1.1, H2.1, H3.1, H4.1, IC1.10 (~LBL), IC1.11 (~UBL), IC1.18 (GND_1), IC1.19 (GND_2), IC1.35 (GND_3), IC1.38 (GND_4), IC1.57 (GND_5), IC1.58 (GND_6), IC1.61 (GND_7), IC1.64 (~CE0R), IC1.65 (~UBR), IC1.66 (~LBR), IC1.88 (GND_8), J1.1, J1.3, J2.2, J3.1, J3.2, J3.5, J3.6, J3.11, J3.12, J3.17, J3.18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
unnamed: R4.2, SW2.2, U24.2 (VDD)
unnamed: C22.1, R2.1, TP35.1, U17.1
unnamed: D1.2 (A), U19.6
unnamed: D1.1 (K), R3.1
unnamed: D2.2 (A), U21.8
unnamed: D2.1 (K), R6.1
unnamed: D3.2 (A), U19.10
unnamed: D3.1 (K), R7.1
unnamed: IC1.13 (CE1L), U67.22 (I/O)
unnamed: IC1.12 (~CE0L), U67.23 (I/O)
unnamed: JP1.2 (B), R61.2
unnamed: R1.2, R2.2, SW1.2, TP31.1
unnamed: TP34.1, U18.11, U19.1
unnamed: TP38.1, U18.2, U19.2
unnamed: TP40.1, U18.3, U18.4
unnamed: TP41.1, U18.10, U19.4
unnamed: TP47.1, U18.8, U19.9
unnamed: TP49.1, U18.5, U19.8
unnamed: TP50.1, U18.6, U20.1
unnamed: TP71.1, U51.2, U52.4
unnamed: U1.2, U2.11 (Cp), U3.11 (Cp), U4.11 (Cp)
unnamed: U8.14 (I/O), U9.9 (IN)
unnamed: U8.15 (I/O), U9.8 (IN)
unnamed: U8.16 (I/O), U9.7 (IN)
unnamed: U8.17 (I/O), U9.6 (IN)
unnamed: U19.11, U19.12
unnamed: U21.2, U21.3
unnamed: U21.4, U21.5
unnamed: U21.6, U21.11, U23.1, U23.4, U23.9, U23.12
unnamed: TP37.1, U17.2, U22.3 (D0)
unnamed: U19.3, U22.5 (Q1)
unnamed: TP69.1, U25.15 (O0), U26.25 (2~OE), U26.48 (1~OE)
unnamed: TP70.1, U25.14 (O1), U27.25 (2~OE), U27.48 (1~OE)
unnamed: U31.25 (2~OE), U31.48 (1~OE), U33.15 (O0)
unnamed: U32.25 (2~OE), U32.48 (1~OE), U33.14 (O1)
unnamed: U33.13 (O2), U34.25 (2~OE), U34.48 (1~OE)
unnamed: U33.12 (O3), U35.25 (2~OE), U35.48 (1~OE)
unnamed: U36.25 (2~OE), U36.48 (1~OE), U37.15 (O0)
unnamed: U37.14 (O1), U38.25 (2~OE), U38.48 (1~OE)
unnamed: U37.13 (O2), U39.25 (2~OE), U39.48 (1~OE)
unnamed: U37.12 (O3), U40.25 (2~OE), U40.48 (1~OE)
unnamed: TP72.1, U51.1, U52.2, U53.49 (RS1)
unnamed: TP73.1, U54.3, U55.25 (2CLK), U55.48 (1CLK), U56.25 (2CLK), U56.48 (1CLK)
unnamed: U59.1, U60.2
unnamed: U59.2, U60.4
unnamed: U67.21 (I/O), U68.9 (E1), U68.10 (E2)
unnamed: U60.12, U68.15 (Mr)
VCC: C1.1, C2.1, C3.1, C4.1, C5.1, C6.1, C7.1, C8.1, C9.1, C10.1, C11.1, C12.1, C13.1, C14.1, C15.1, C16.1, C17.1, C18.1, C19.1, C20.1, C21.1, C23.1, C24.1, C25.1, C26.1, C27.1, C28.1, C29.1, C30.1, C31.1, C32.1, C33.1, C34.1, C35.1, C36.1, C37.1, C38.1, C39.1, C40.1, C41.1, C42.1, C43.1, C44.1, C45.1, C46.1, C47.1, C48.1, C49.1, C50.1, C51.1, C52.1, C53.1, C54.1, C55.1, C56.1, C57.1, C58.1, C59.1, C60.1, C61.1, C62.1, C63.1, C64.1, C65.1, C66.1, C67.1, C68.1, C69.1, C70.1, C71.1, C72.1, IC1.14 (~SEML), IC1.15 (VCC_1), IC1.28 (VCC_2), IC1.46 (VCC_3), IC1.60 (R/~WR), IC1.62 (~SEMR), IC1.63 (CE1R), IC1.87 (M/~S), J2.1, J3.63, J3.64, OSC1.14 (Vcc), R1.1, R4.1, R5.1, R61.1, U1.3, U1.5, U1.9, U1.11, U1.13, U1.14 (VCC), U2.20 (VCC), U3.20 (VCC), U4.20 (VCC), U5.24 (VCC), U6.24 (VCC), U7.24 (VCC), U8.24 (VCC)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
